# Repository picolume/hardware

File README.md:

# PicoLume Hardware

Hardware designs for the PicoLume wireless LED prop system. All designs are created in KiCad.

## Design Series

### series-prop (Primary)

The primary hardware design for production use. Contains the **PicoLume Board** - a compact control board designed to be installed on each prop in a synchronized LED light show.

**Current Design: receiver-v1**

An RP2040-based control board featuring:

- RP2040 microcontroller with 16MB flash (W25Q16JVS)
- RFM69HCW radio module (915 MHz) for wireless timecode reception
- USB-C connector for programming and show file upload
- Dual power input with automatic switching (LM66200)
- 5V buck converter (AP63205WU) for LED strip power
- Pinout for 0.91" OLED display (I2C)
- Screw terminals for LED strip connection (WS2812B)
- Level shifter (74AHCT1G125) for reliable LED data signal
- Three tactile buttons for configuration
- Onboard WS2812B status LED
- Four M3 mounting holes

The PicoLume Board is the core control component. A complete receiver or transmitter setup requires additional hardware (enclosures, power supplies, antennas, etc.) which are currently being designed.

### series-legacy (Prototypes)

Early prototype designs from the development phase. These boards were used for proof-of-concept testing and firmware development.

**Note:** These designs are prototypes and are not suited for production use.

| Version | Description                   |
| ------- | ----------------------------- |
| v1      | Initial RFM69-based design    |
| v2      | RP2040 with Pi Pico footprint |
| v3      | Refined RP2040 design         |
| v4      | RP2350 Experiment             |

## Related Repositories

- **firmware/** - Arduino firmware for receiver and remote devices

## License

See [LICENSE](LICENSE) for details.

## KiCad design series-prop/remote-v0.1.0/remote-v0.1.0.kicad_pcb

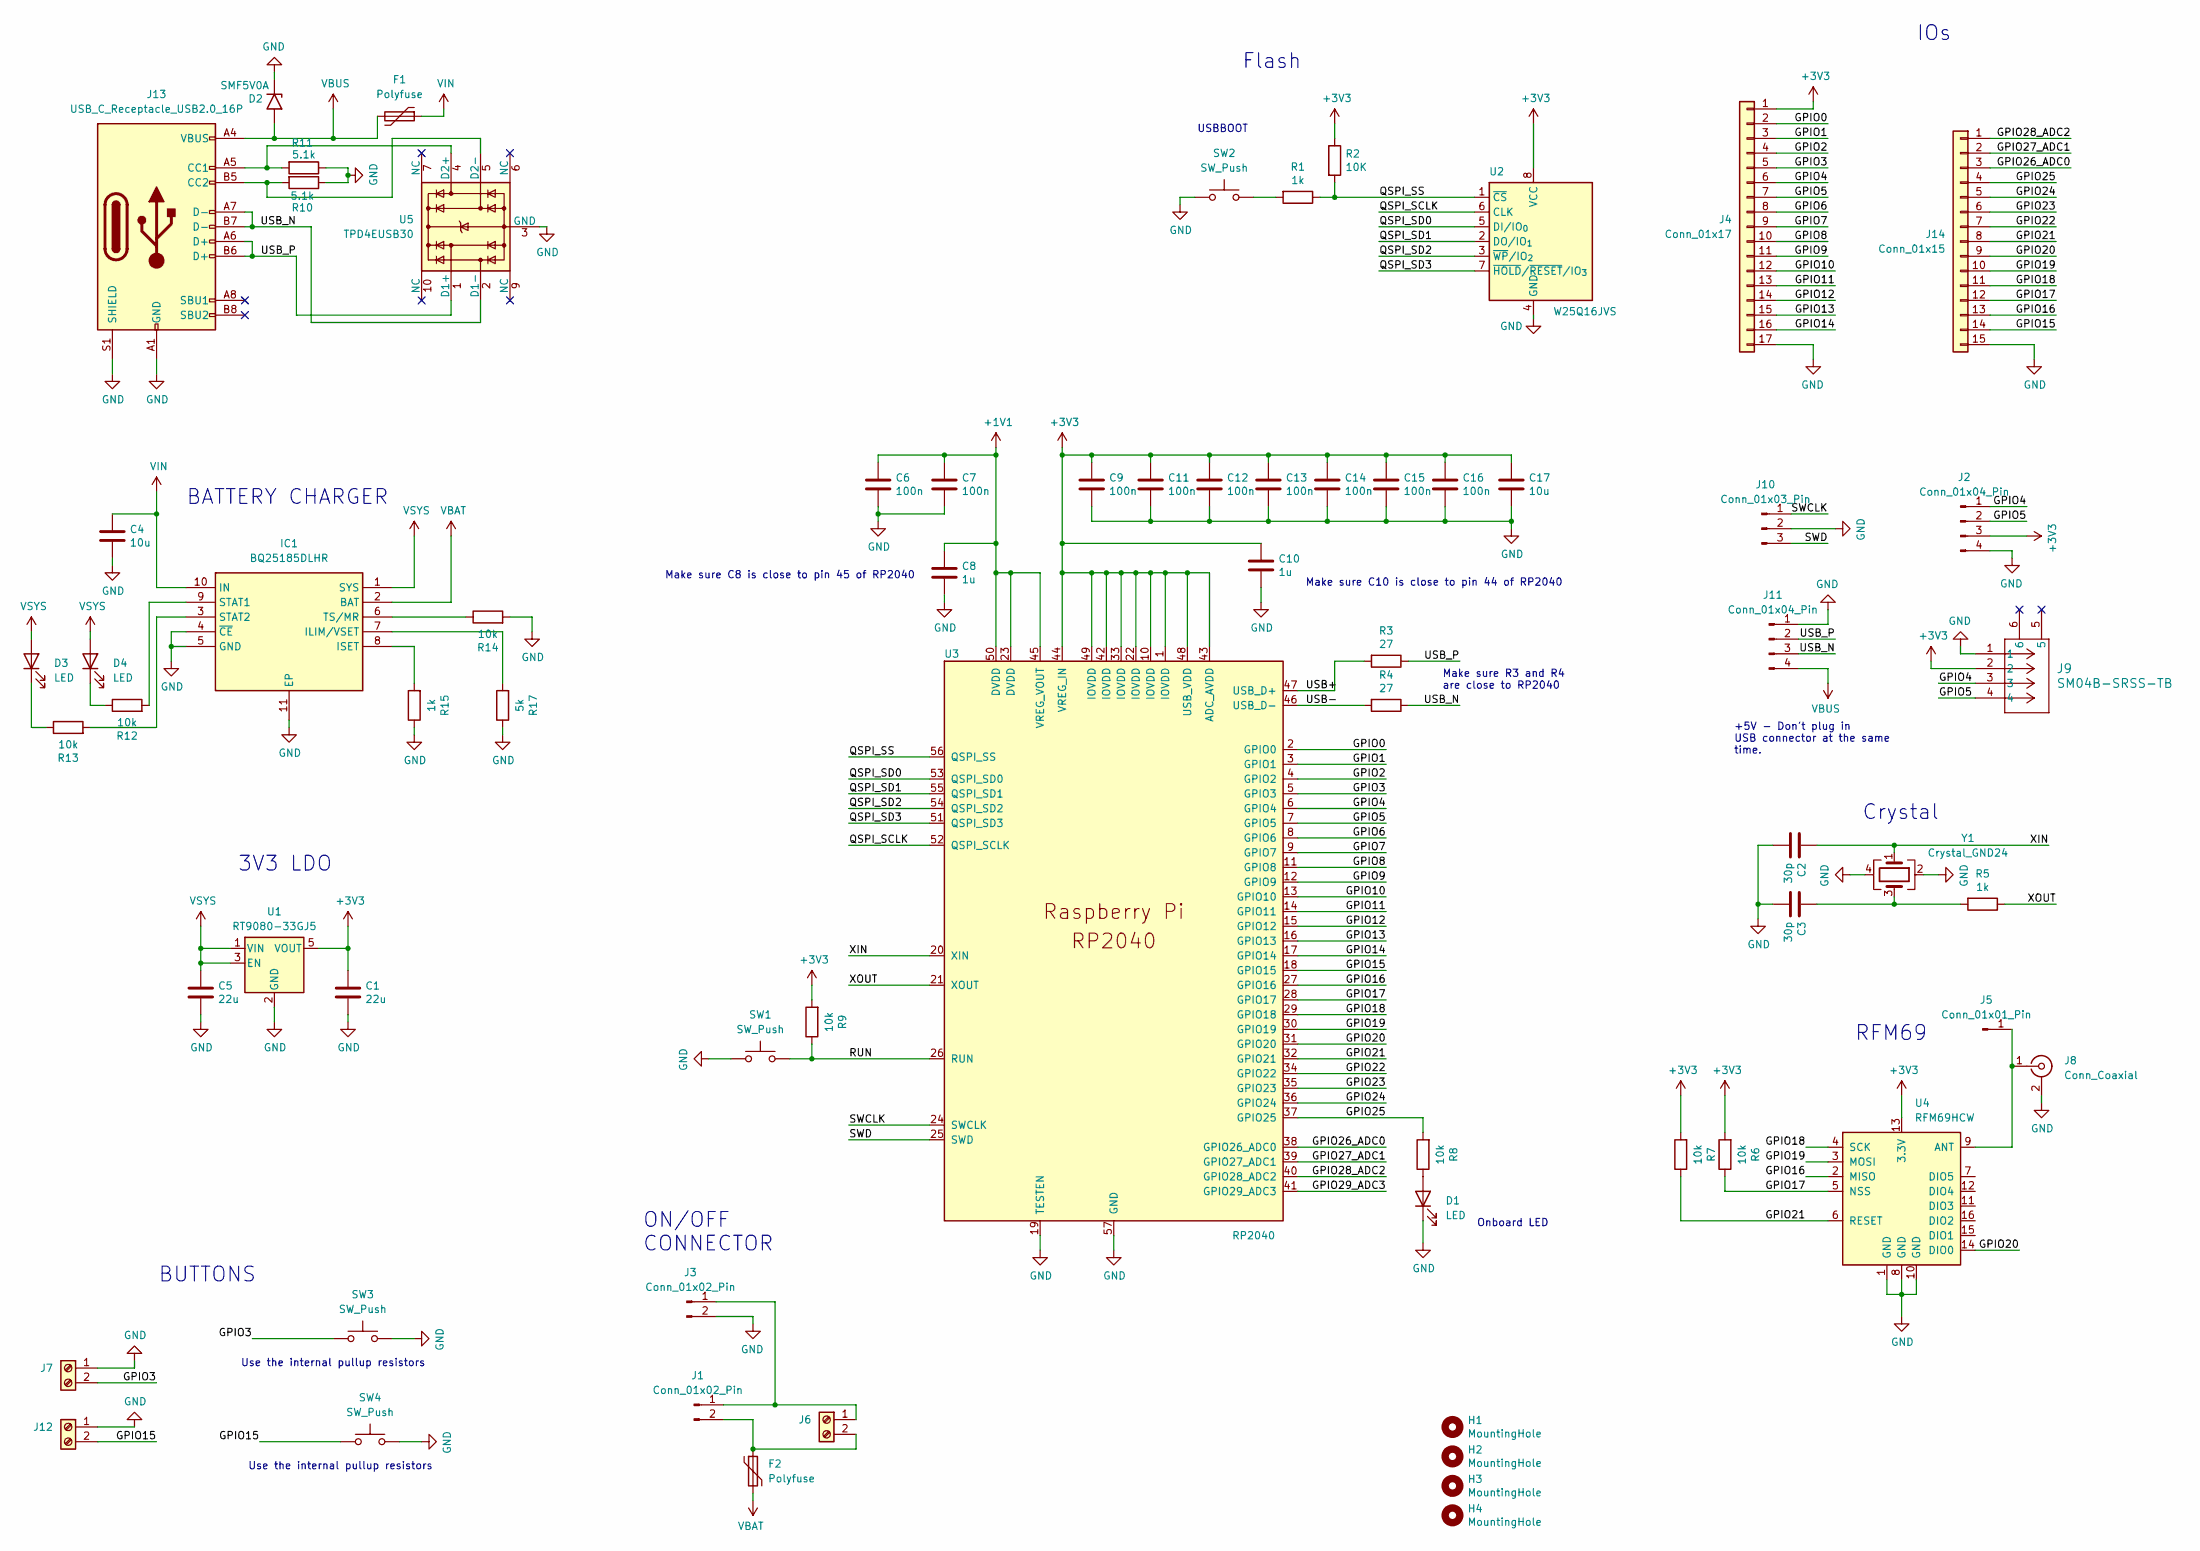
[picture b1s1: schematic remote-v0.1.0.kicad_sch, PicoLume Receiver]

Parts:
C1, C5: 22u; C_0805_2012Metric; LCSC C45783
C2, C3: 30p; C_0603_1608Metric; LCSC C1658
C4, C17: 10u; C_0603_1608Metric; LCSC C14663
C6, C7, C9, C11, C12, C13, C14, C15, C16: 100n; C_0603_1608Metric; LCSC C14663
C8, C10: 1u; C_0603_1608Metric; LCSC C15849
D1, D3, D4: LED; LED_0603_1608Metric; LCSC C2286
D2: SMF5V0A; D_SMF; LCSC C151296
F1, F2: Polyfuse; Fuse_1210_3225Metric; LCSC C20617440
H1, H2, H3, H4: MountingHole; MountingHole_3.2mm_M3
IC1: BQ25185DLHR; SON40P220X200X80-11N; Mouser Part Number 595-BQ25185DLHR
J1: Conn_01x02_Pin; PinHeader_1x02_P2.54mm_Vertical
J2, J11: Conn_01x04_Pin; PinHeader_1x04_P2.54mm_Vertical
J3: Conn_01x02_Pin; JST_PH_S2B-PH-K_1x02_P2.00mm_Horizontal
J4: Conn_01x17; PinHeader_1x17_P2.54mm_Vertical
J5: Conn_01x01_Pin; PinHeader_1x01_P2.54mm_Vertical
J6, J7, J12: Screw_Terminal_01x02; TerminalBlock_bornier-2_P5.08mm
J8: Conn_Coaxial; U.FL_Hirose_U.FL-R-SMT-1_Vertical; LCSC C88374
J9: SM04B-SRSS-TB; CONN_SM04B-SRSS-TB_JST
J10: Conn_01x03_Pin; PinHeader_1x03_P2.54mm_Vertical
J13: USB_C_Receptacle_USB2.0_16P; USB_C_Receptacle_HRO_TYPE-C-31-M-12; LCSC C165948
J14: Conn_01x15; PinHeader_1x15_P2.54mm_Vertical
R1, R15: 1k; R_0603_1608Metric; LCSC C21190
R2: 10K; R_0603_1608Metric; LCSC C25804
R3, R4: 27; R_0603_1608Metric; LCSC C22941
R5: 1k; R_0603_1608Metric
R6, R7, R8, R9, R12, R13, R14: 10k; R_0603_1608Metric; LCSC C25804
R10, R11: 5.1k; R_0603_1608Metric; LCSC C23186
R17: 5k; R_0603_1608Metric; LCSC C166926
SW1, SW2, SW3, SW4: SW_Push; SW_Tactile_SPST_NO_Straight_CK_PTS636Sx25SMTRLFS; LCSC C609852
U1: RT9080-33GJ5; SOT-23-5; LCSC C841192
U2: W25Q16JVS; SOIC-8_5.3x5.3mm_P1.27mm; LCSC C131025
U3: RP2040; QFN-56-1EP_7x7mm_P0.4mm_EP3.2x3.2mm; LCSC C2040
U4: RFM69HCW; HOPERF_RFM9XW_SMD; LCSC C2844478
U5: TPD4EUSB30; USON-10_2.5x1.0mm_P0.5mm; LCSC C90627
Y1: Crystal_GND24; Crystal_SMD_3225-4Pin_3.2x2.5mm; LCSC C9002

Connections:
+1V1: C6.1, C7.1, C8.1, U3.23 (DVDD), U3.45 (VREG_VOUT), U3.50 (DVDD)
+3V3: C1.1, C9.1, C10.1, C11.1, C12.1, C13.1, C14.1, C15.1, C16.1, C17.1, J2.3, J4.1, J9.2, R2.1, R6.2, R7.2, R9.2, U1.5 (VOUT), U2.8 (VCC), U3.1 (IOVDD), U3.10 (IOVDD), U3.22 (IOVDD), U3.33 (IOVDD), U3.42 (IOVDD), U3.43 (ADC_AVDD), U3.44 (VREG_IN), U3.48 (USB_VDD), U3.49 (IOVDD), U4.13 (3.3V)
/GPIO0: J4.2, U3.2 (GPIO0)
/GPIO1: J4.3, U3.3 (GPIO1)
/GPIO2: J4.4, U3.4 (GPIO2)
/GPIO3: J4.5, J7.2, SW3.2, U3.5 (GPIO3)
/GPIO4: J2.1, J4.6, J9.3, U3.6 (GPIO4)
/GPIO5: J2.2, J4.7, J9.4, U3.7 (GPIO5)
/GPIO6: J4.8, U3.8 (GPIO6)
/GPIO7: J4.9, U3.9 (GPIO7)
/GPIO8: J4.10, U3.11 (GPIO8)
/GPIO9: J4.11, U3.12 (GPIO9)
/GPIO10: J4.12, U3.13 (GPIO10)
/GPIO11: J4.13, U3.14 (GPIO11)
/GPIO12: J4.14, U3.15 (GPIO12)
/GPIO13: J4.15, U3.16 (GPIO13)
/GPIO14: J4.16, U3.17 (GPIO14)
/GPIO15: J12.2, J14.14, SW4.2, U3.18 (GPIO15)
/GPIO16: J14.13, U3.27 (GPIO16), U4.2 (MISO)
/GPIO17: J14.12, R6.1, U3.28 (GPIO17), U4.5 (NSS)
/GPIO18: J14.11, U3.29 (GPIO18), U4.4 (SCK)
/GPIO19: J14.10, U3.30 (GPIO19), U4.3 (MOSI)
/GPIO20: J14.9, U3.31 (GPIO20), U4.14 (DIO0)
/GPIO21: J14.8, R7.1, U3.32 (GPIO21), U4.6 (RESET)
/GPIO22: J14.7, U3.34 (GPIO22)
/GPIO23: J14.6, U3.35 (GPIO23)
/GPIO24: J14.5, U3.36 (GPIO24)
/GPIO25: J14.4, R8.2, U3.37 (GPIO25)
/GPIO26_ADC0: J14.3, U3.38 (GPIO26_ADC0)
/GPIO27_ADC1: J14.2, U3.39 (GPIO27_ADC1)
/GPIO28_ADC2: J14.1, U3.40 (GPIO28_ADC2)
/GPIO29_ADC3: U3.41 (GPIO29_ADC3)
/QSPI_SCLK: U2.6 (CLK), U3.52 (QSPI_SCLK)
/QSPI_SD0: U2.5 (DI/IO_{0}), U3.53 (QSPI_SD0)
/QSPI_SD1: U2.2 (DO/IO_{1}), U3.55 (QSPI_SD1)
/QSPI_SD2: U2.3 (~WP/IO_{2}), U3.54 (QSPI_SD2)
/QSPI_SD3: U2.7 (~HOLD/~RESET/IO_{3}), U3.51 (QSPI_SD3)
/QSPI_SS: R1.1, R2.2, U2.1 (~CS), U3.56 (QSPI_SS)
/RUN: R9.1, SW1.2, U3.26 (RUN)
/SWCLK: J10.1, U3.24 (SWCLK)
/SWD: J10.3, U3.25 (SWD)
/USB+: R3.2, U3.47 (USB_D+)
/USB-: R4.2, U3.46 (USB_D-)
/USB_N: J11.3, J13.A7 (D-), J13.B7 (D-), R4.1, U5.2 (D1-)
/USB_P: J11.2, J13.A6 (D+), J13.B6 (D+), R3.1, U5.1 (D1+)
/XIN: C2.1, U3.20 (XIN), Y1.1
/XOUT: R5.1, U3.21 (XOUT)
GND: C1.2, C2.2, C3.2, C4.2, C5.2, C6.2, C7.2, C8.2, C9.2, C10.2, C11.2, C12.2, C13.2, C14.2, C15.2, C16.2, C17.2, D1.1 (K), D2.1 (A1), IC1.4 (~CE), IC1.5 (GND), IC1.11 (EP), J2.4, J3.2, J4.17, J7.1, J8.2 (Ext), J9.1, J10.2, J11.1, J12.1, J13.A1 (GND), J13.A12 (GND), J13.B1 (GND), J13.B12 (GND), J13.S1 (SHIELD), J14.15, R10.1, R11.1, R14.2, R15.1, R17.1, SW1.1, SW2.1, SW3.1, SW4.1, U1.2 (GND), U2.4 (GND), U3.19 (TESTEN), U3.57 (GND), U4.1 (GND), U4.8 (GND), U4.10 (GND), U5.3 (GND), U5.8 (GND), Y1.2, Y1.4
unnamed: C3.1, R5.2, Y1.3
unnamed: D1.2 (A), R8.1
unnamed: D3.1 (K), R13.1
unnamed: D4.1 (K), R12.1
unnamed: IC1.7 (ILIM/VSET), R17.2
unnamed: IC1.8 (ISET), R15.2
unnamed: IC1.9 (STAT1), R12.2
unnamed: IC1.3 (STAT2), R13.2
unnamed: IC1.6 (TS/MR), R14.1
unnamed: J1.1, J3.1, J6.1
unnamed: F2.1, J1.2, J6.2
unnamed: J5.1, J8.1 (In), U4.9 (ANT)
unnamed: J13.A5 (CC1), R11.2, U5.4 (D2+)
unnamed: J13.B5 (CC2), R10.2, U5.5 (D2-)
unnamed: R1.2, SW2.2
VBAT: F2.2, IC1.2 (BAT)
VBUS: D2.2 (A2), F1.2, J11.4, J13.A4 (VBUS), J13.A9 (VBUS), J13.B4 (VBUS), J13.B9 (VBUS)
VIN: C4.1, F1.1, IC1.10 (IN)
VSYS: C5.1, D3.2 (A), D4.2 (A), IC1.1 (SYS), U1.1 (VIN), U1.3 (EN)

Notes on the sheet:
Use the internal pullup resistors
RFM69
IOs
Crystal
Make sure C8 is close to pin 45 of RP2040
+5V - Don't plug in USB connector at the same time.
BUTTONS
USBBOOT
Make sure C10 is close to pin 44 of RP2040
ON/OFF CONNECTOR
Onboard LED
BATTERY CHARGER
3V3 LDO
Make sure R3 and R4 are close to RP2040
Flash

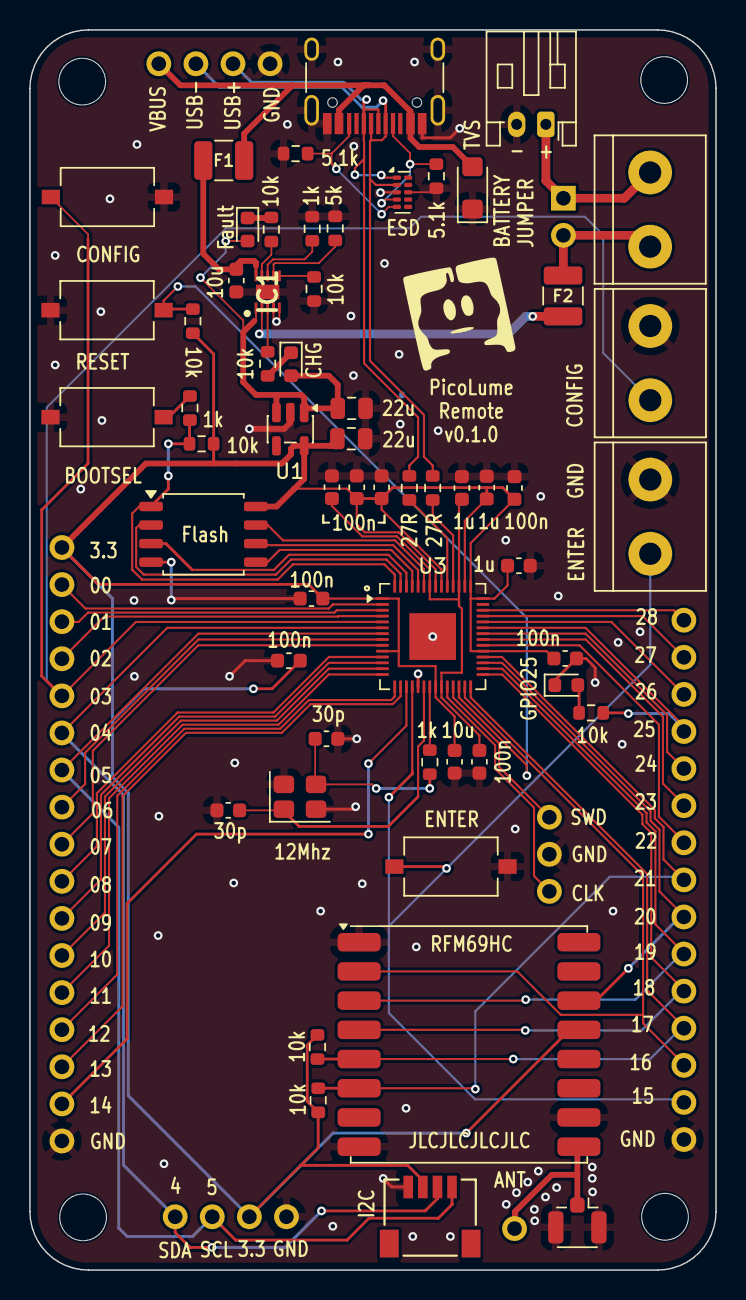
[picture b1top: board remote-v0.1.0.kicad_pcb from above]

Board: 2 copper layers, 47.0 x 84.9 mm, 68 parts (0 on the bottom side), 66 nets.

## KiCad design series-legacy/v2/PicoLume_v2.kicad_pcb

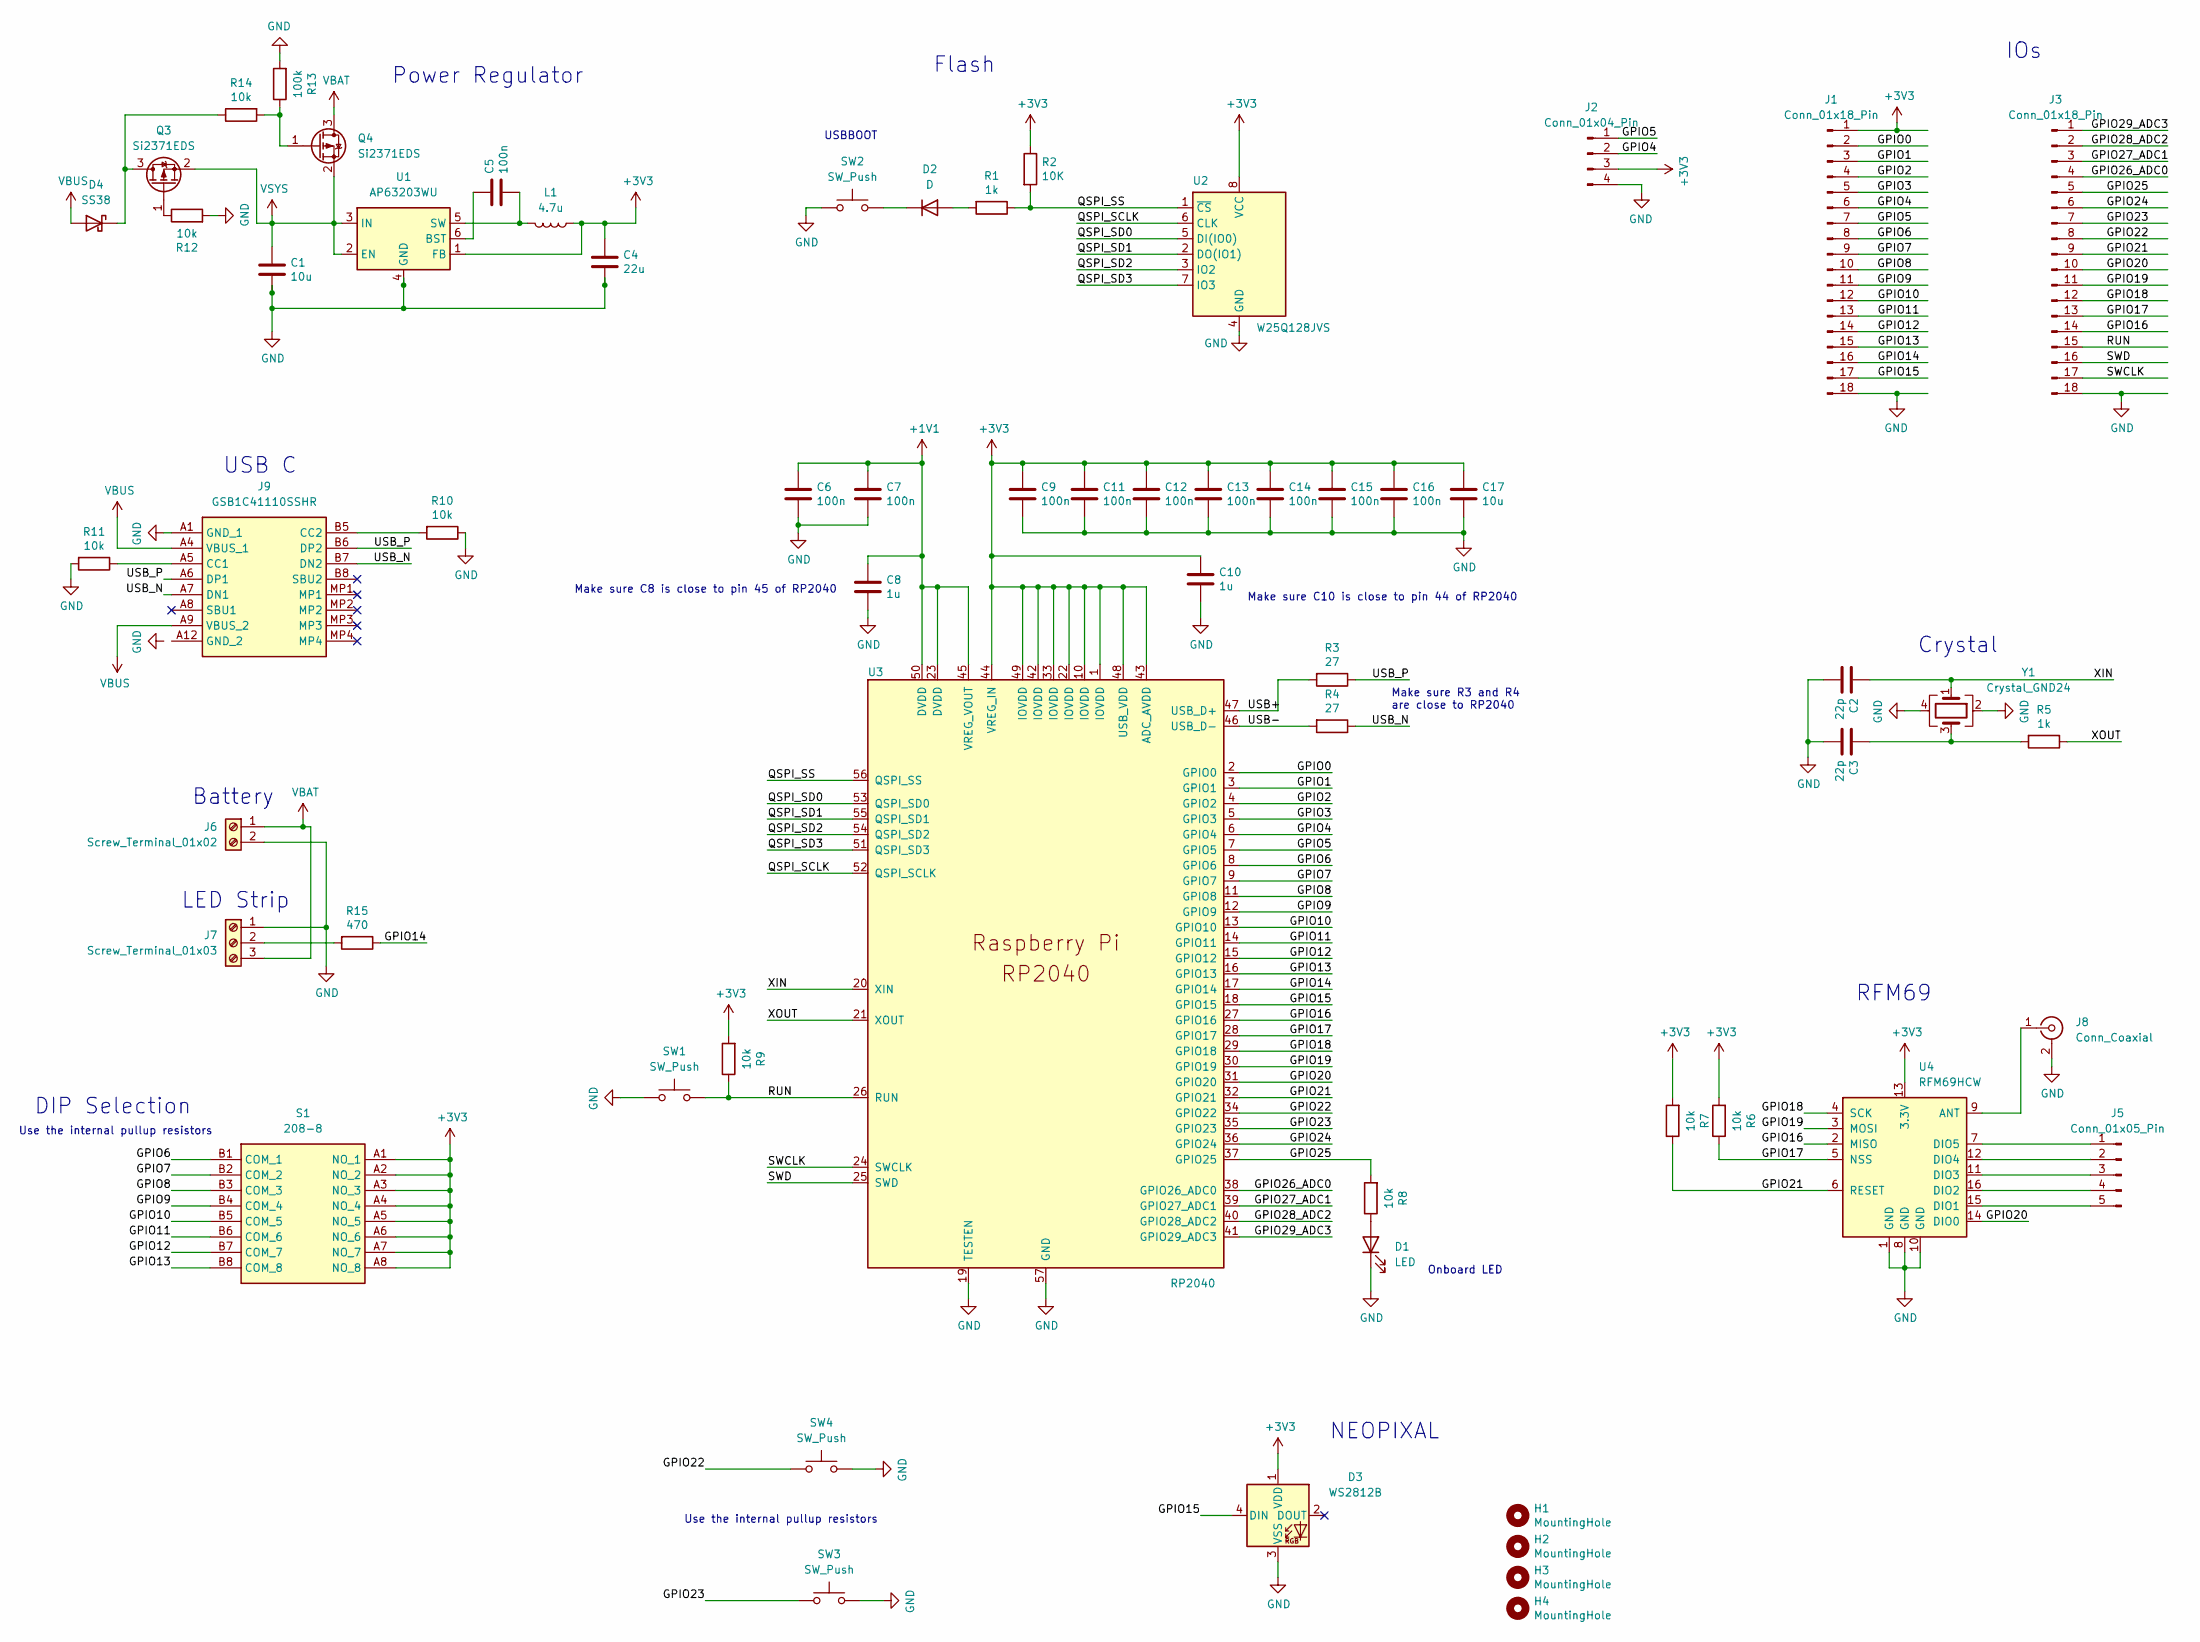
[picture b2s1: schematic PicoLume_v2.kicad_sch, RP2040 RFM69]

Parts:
C1, C17: 10u; C_0603_1608Metric
C2, C3: 22p; C_0603_1608Metric
C4: 22u; C_0603_1608Metric
C5, C6, C7, C9, C11, C12, C13, C14, C15, C16: 100n; C_0603_1608Metric
C8, C10: 1u; C_0603_1608Metric
D1: LED; LED_0603_1608Metric
D2: D; D_0603_1608Metric
D3: WS2812B; LED_WS2812B_PLCC4_5.0x5.0mm_P3.2mm
D4: SS38; D_SMA
H1, H2, H3, H4: MountingHole; MountingHole_2.7mm_M2.5
J1, J3: Conn_01x18_Pin; PinHeader_1x18_P2.54mm_Vertical
J2: Conn_01x04_Pin; PinHeader_1x04_P2.54mm_Vertical
J5: Conn_01x05_Pin; PinHeader_1x05_P2.54mm_Vertical
J6: Screw_Terminal_01x02; TerminalBlock_bornier-2_P5.08mm
J7: Screw_Terminal_01x03; TerminalBlock_bornier-3_P5.08mm
J8: Conn_Coaxial; U.FL_Molex_MCRF_73412-0110_Vertical
J9: GSB1C41110SSHR; Manufacturer_Part_Number GSB1C41110SSHR
L1: 4.7u; VLS5045EX330M
Q3, Q4: Si2371EDS; SOT-23
R1, R5: 1k; R_0603_1608Metric
R2: 10K; R_0603_1608Metric
R3, R4: 27; R_0603_1608Metric
R6, R7, R8, R9, R10, R11, R12, R14: 10k; R_0603_1608Metric
R13: 100k; R_0603_1608Metric
R15: 470; R_0603_1608Metric
S1: 208-8; 2088; Mouser Part Number 774-2088
SW1, SW2, SW3, SW4: SW_Push; FSMH
U1: AP63203WU; TSOT-23-6
U2: W25Q128JVS; SOIC-8_5.23x5.23mm_P1.27mm
U3: RP2040; RP2040-QFN-56
U4: RFM69HCW; MOD_COM-13909
Y1: Crystal_GND24; ABM810000MHZ12D2W

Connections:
+1V1: C6.1, C7.1, C8.1, U3.23 (DVDD), U3.45 (VREG_VOUT), U3.50 (DVDD)
+3V3: C4.1, C9.1, C10.1, C11.1, C12.1, C13.1, C14.1, C15.1, C16.1, C17.1, D3.1 (VDD), J1.1, J2.3, L1.1, R2.1, R6.2, R7.2, R9.2, S1.A1 (NO_1), S1.A2 (NO_2), S1.A3 (NO_3), S1.A4 (NO_4), S1.A5 (NO_5), S1.A6 (NO_6), S1.A7 (NO_7), S1.A8 (NO_8), U1.1 (FB), U2.8 (VCC), U3.1 (IOVDD), U3.10 (IOVDD), U3.22 (IOVDD), U3.33 (IOVDD), U3.42 (IOVDD), U3.43 (ADC_AVDD), U3.44 (VREG_IN), U3.48 (USB_VDD), U3.49 (IOVDD), U4.13 (3.3V)
/GPIO0: J1.2, U3.2 (GPIO0)
/GPIO1: J1.3, U3.3 (GPIO1)
/GPIO2: J1.4, U3.4 (GPIO2)
/GPIO3: J1.5, U3.5 (GPIO3)
/GPIO4: J1.6, J2.2, U3.6 (GPIO4)
/GPIO5: J1.7, J2.1, U3.7 (GPIO5)
/GPIO6: J1.8, S1.B1 (COM_1), U3.8 (GPIO6)
/GPIO7: J1.9, S1.B2 (COM_2), U3.9 (GPIO7)
/GPIO8: J1.10, S1.B3 (COM_3), U3.11 (GPIO8)
/GPIO9: J1.11, S1.B4 (COM_4), U3.12 (GPIO9)
/GPIO10: J1.12, S1.B5 (COM_5), U3.13 (GPIO10)
/GPIO11: J1.13, S1.B6 (COM_6), U3.14 (GPIO11)
/GPIO12: J1.14, S1.B7 (COM_7), U3.15 (GPIO12)
/GPIO13: J1.15, S1.B8 (COM_8), U3.16 (GPIO13)
/GPIO14: J1.16, R15.1, U3.17 (GPIO14)
/GPIO15: D3.4 (DIN), J1.17, U3.18 (GPIO15)
/GPIO16: J3.14, U3.27 (GPIO16), U4.2 (MISO)
/GPIO17: J3.13, R6.1, U3.28 (GPIO17), U4.5 (NSS)
/GPIO18: J3.12, U3.29 (GPIO18), U4.4 (SCK)
/GPIO19: J3.11, U3.30 (GPIO19), U4.3 (MOSI)
/GPIO20: J3.10, U3.31 (GPIO20), U4.14 (DIO0)
/GPIO21: J3.9, R7.1, U3.32 (GPIO21), U4.6 (RESET)
/GPIO22: J3.8, SW4.2, U3.34 (GPIO22)
/GPIO23: J3.7, SW3.2, U3.35 (GPIO23)
/GPIO24: J3.6, U3.36 (GPIO24)
/GPIO25: J3.5, R8.2, U3.37 (GPIO25)
/GPIO26_ADC0: J3.4, U3.38 (GPIO26_ADC0)
/GPIO27_ADC1: J3.3, U3.39 (GPIO27_ADC1)
/GPIO28_ADC2: J3.2, U3.40 (GPIO28_ADC2)
/GPIO29_ADC3: J3.1, U3.41 (GPIO29_ADC3)
/QSPI_SCLK: U2.6 (CLK), U3.52 (QSPI_SCLK)
/QSPI_SD0: U2.5 (DI(IO0)), U3.53 (QSPI_SD0)
/QSPI_SD1: U2.2 (DO(IO1)), U3.55 (QSPI_SD1)
/QSPI_SD2: U2.3 (IO2), U3.54 (QSPI_SD2)
/QSPI_SD3: U2.7 (IO3), U3.51 (QSPI_SD3)
/QSPI_SS: R1.1, R2.2, U2.1 (~CS), U3.56 (QSPI_SS)
/RUN: J3.15, R9.1, SW1.2, U3.26 (RUN)
/SWCLK: J3.17, U3.24 (SWCLK)
/SWD: J3.16, U3.25 (SWD)
/USB+: R3.2, U3.47 (USB_D+)
/USB-: R4.2, U3.46 (USB_D-)
/USB_N: J9.A7 (DN1), J9.B7 (DN2), R4.1
/USB_P: J9.A6 (DP1), J9.B6 (DP2), R3.1
/XIN: C2.1, U3.20 (XIN), Y1.1
/XOUT: R5.1, U3.21 (XOUT)
GND: C1.2, C2.2, C3.2, C4.2, C6.2, C7.2, C8.2, C9.2, C10.2, C11.2, C12.2, C13.2, C14.2, C15.2, C16.2, C17.2, D1.1 (K), D3.3 (VSS), J1.18, J2.4, J3.18, J6.2, J7.1, J8.2 (Ext), J9.A1 (GND_1), R10.1, R11.2, R12.2, R13.2, SW1.1, SW2.1, SW3.1, SW4.1, U1.4 (GND), U2.4 (GND), U3.19 (TESTEN), U3.57 (GND), U4.1 (GND), U4.8 (GND), U4.10 (GND), Y1.2, Y1.4
unnamed: C3.1, R5.2, Y1.3
unnamed: D1.2 (A), R8.1
unnamed: D2.2 (A), R1.2
unnamed: D2.1 (K), SW2.2
unnamed: D4.1 (K), Q3.3 (D), R14.1
unnamed: J5.1, U4.7 (DIO5)
unnamed: J5.2, U4.12 (DIO4)
unnamed: J5.3, U4.11 (DIO3)
unnamed: J5.4, U4.16 (DIO2)
unnamed: J5.5, U4.15 (DIO1)
unnamed: J7.2, R15.2
unnamed: J8.1 (In), U4.9 (ANT)
unnamed: J9.A5 (CC1), R11.1
unnamed: J9.B5 (CC2), R10.2
unnamed: Q3.1 (G), R12.1
unnamed: Q4.1 (G), R13.1, R14.2
unnamed: C5.1, U1.6 (BST)
unnamed: C5.2, L1.2, U1.5 (SW)
VBAT: J6.1, J7.3, Q4.3 (D)
VBUS: D4.2 (A), J9.A4 (VBUS_1), J9.A9 (VBUS_2)
VSYS: C1.1, Q3.2 (S), Q4.2 (S), U1.2 (EN), U1.3 (IN)

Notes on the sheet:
DIP Selection
Use the internal pullup resistors
NEOPIXAL
RFM69
IOs
Crystal
USB C
Make sure C8 is close to pin 45 of RP2040
Battery
LED Strip
USBBOOT
Power Regulator
Make sure C10 is close to pin 44 of RP2040
Onboard LED
Make sure R3 and R4 are close to RP2040
Flash

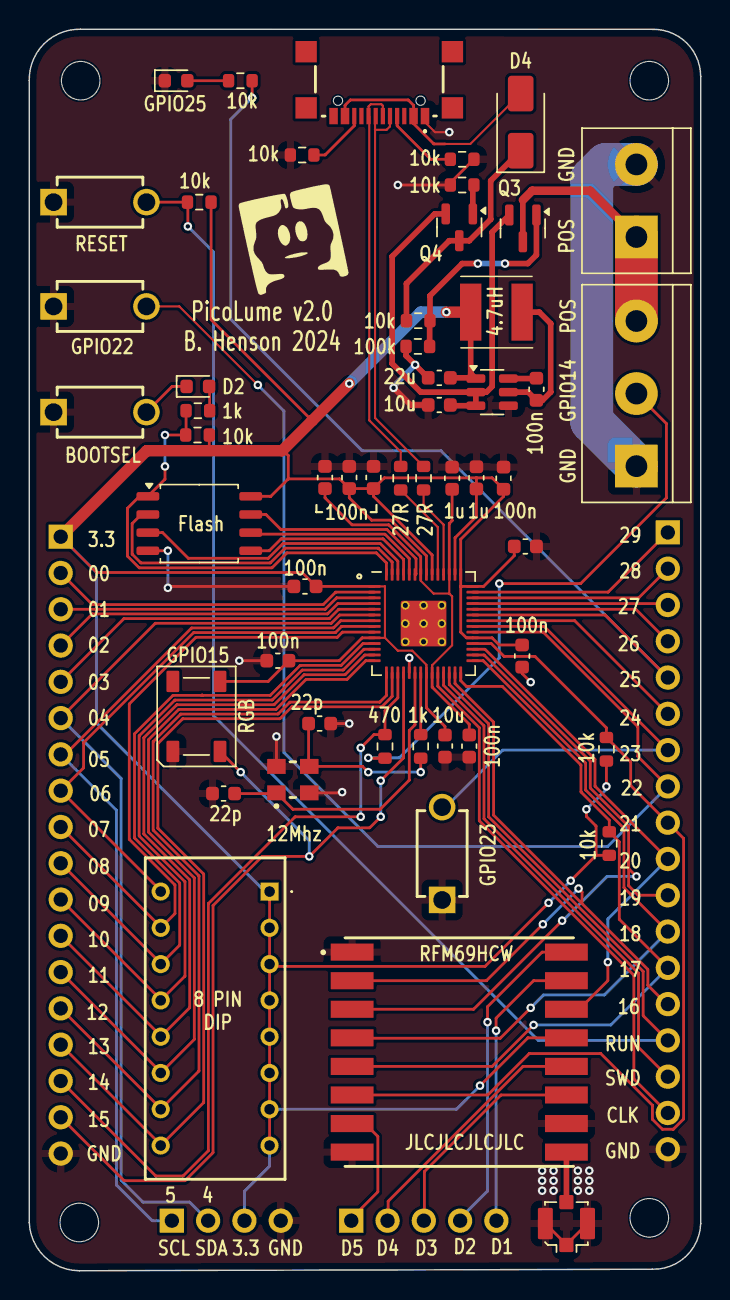
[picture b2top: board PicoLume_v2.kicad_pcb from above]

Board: 2 copper layers, 47.0 x 86.9 mm, 61 parts (0 on the bottom side), 69 nets.
